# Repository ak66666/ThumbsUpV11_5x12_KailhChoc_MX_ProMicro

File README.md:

# ThumbsUp! v11 5x12 Keyboard for Kailh Choc and MX-compatible switches dirven by ProMicro and pin-compatibles

Multilevel 58 Key Ergonomic Contoured Mechanical Keyboard.

A variant of v5 and v8 for this specific combination of switches, plus with extra pins for MCU to make ProGlide Cirque touchpad work in ZMK.
Added slots on the PCBs to cut off the top row and outer columns, to turn the board into a 4x12 or 5x10 or 4x10, moved the tracks out of the way for those cuts.

The board uses Kailh Choc and MX-compatible switches with hot-swap sockets.

ProMicro or pin-compatible MCUs are supported, including Raspberry RP2040, nice!nano v2 and clones.

Supports Proglide Cirque touchpad (up to 40mm diameter).

Can be made wireless with nice!nano v2 (or a clone) and a battery, [ZMK firmware.](https://github.com/ak66666/zmk-config/tree/master)

# Photos

See more pictures in Photos folder. 

# Firmware
Default firmware is here:

Note this board uses the firmware from v5 - it got the very same wiring.

# Here you can buy it

# More info

Usage instructions and miscellaneous info:

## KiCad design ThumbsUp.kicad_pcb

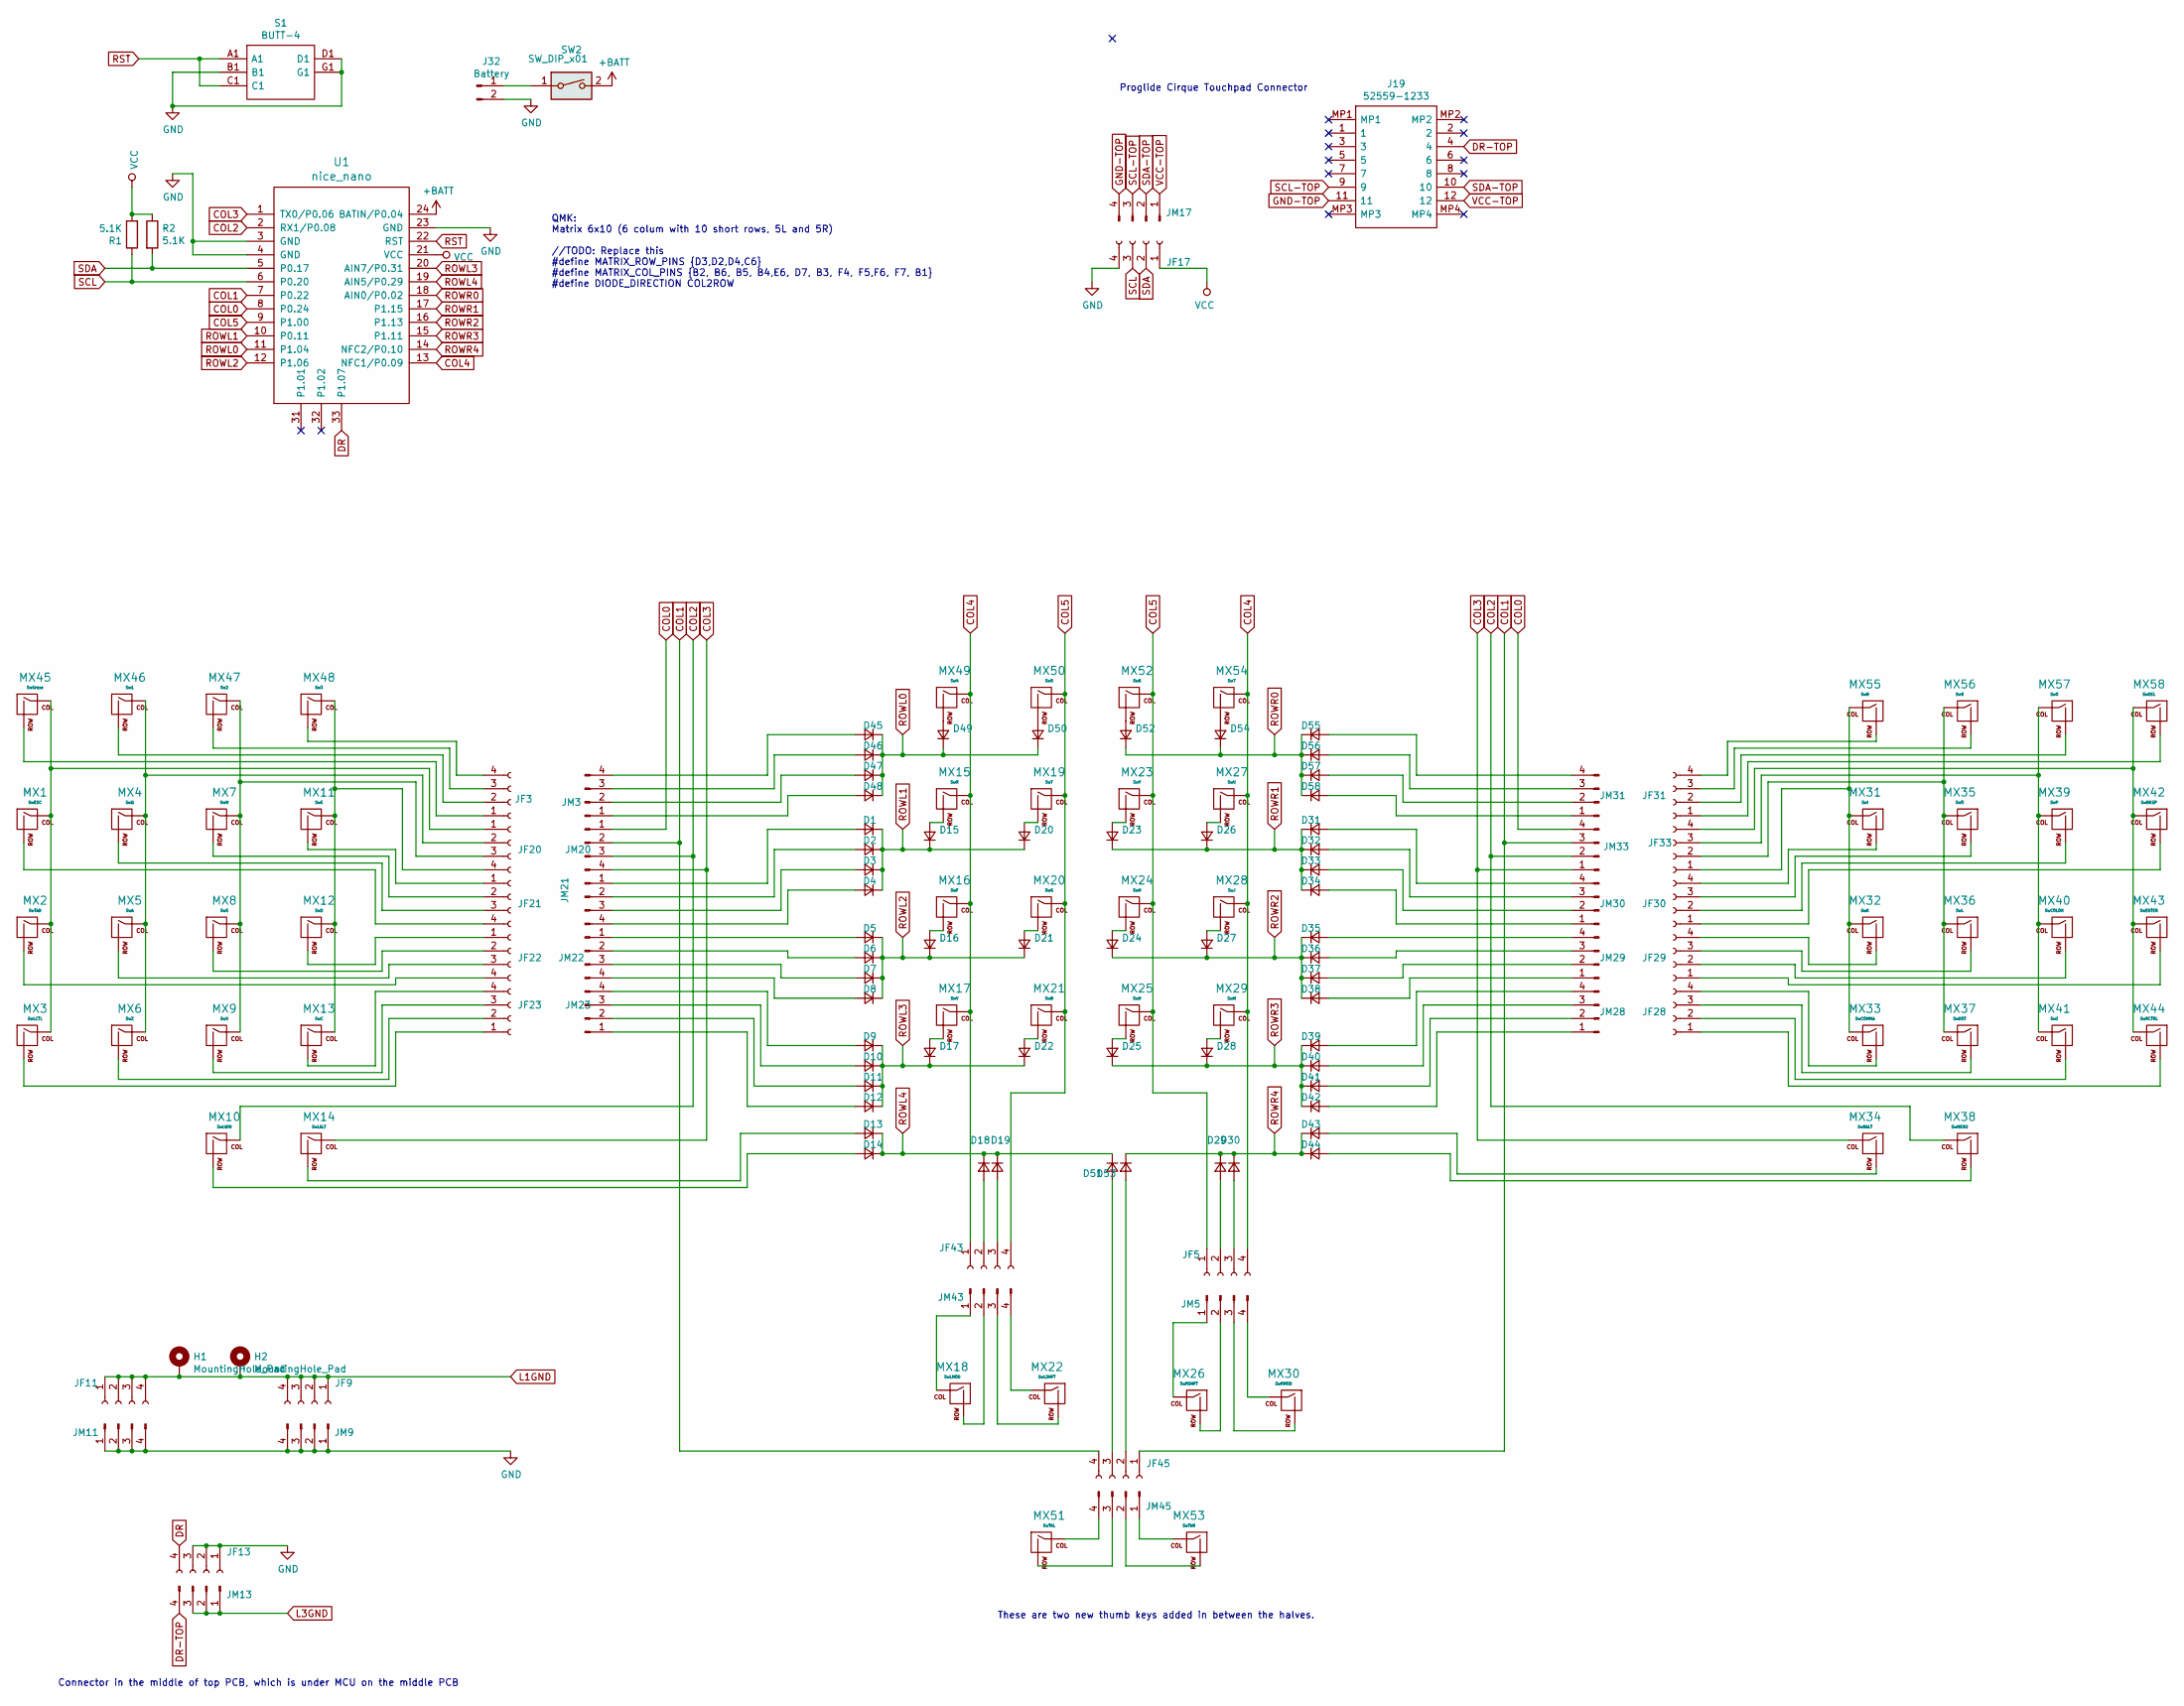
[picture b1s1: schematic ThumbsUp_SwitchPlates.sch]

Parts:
D1, D2, D3, D4, D5, D6, D7, D8, D9, D10, D11, D12, D13, D14, D15, D16, D17, D18, D19, D20, D21, D22, D23, D24, D25, D26, D27, D28, D29, D30, D31, D32, D33, D34, D35, D36, D37, D38, D39, D40, D41, D42, D43, D44, D45, D46, D47, D48, D49, D50, D51, D52, D53, D54, D55, D56, D57, D58: D_Small; D_SOD-523
H1: MountingHole_Pad; MountingHole_6mm_Pad_Via
H2: MountingHole_Pad; MountingHole_8.4mm_M8_Pad_Via
J19: 52559-1233; 525591233; Mouser Part Number 538-52559-1233
J32: Battery; PinHeader_1x02_P2.54mm_Vertical
JF3, JF5, JF20, JF21, JF22, JF23, JF28, JF29, JF30, JF31, JF33, JF43, JF45: Conn_01x04_Female; PinSocket_1x04_P2.54mm_Vertical
JF9, JF11, JF13, JF17: Raiser_Female; PinSocket_1x04_P2.54mm_Vertical
JM3, JM20, JM21, JM22, JM23, JM28, JM29, JM30, JM31, JM33, JM43, JM45: Conn_01x04_Male; PinHeader_1x04_P2.54mm_Vertical
JM5: Male; PinHeader_1x04_P2.54mm_Vertical
JM9, JM11, JM13, JM17: Raiser_Male; PinHeader_1x04_P2.54mm_Vertical
MX1: SwESC; PG1350_MX_sockets
MX2: SwTAB; PG1350_MX_sockets
MX3: SwLCTL; PG1350_MX_sockets
MX4: SwQ; PG1350_MX_sockets
MX5: SwA; PG1350_MX_sockets
MX6: SwZ; PG1350_MX_sockets
MX7: SwW; PG1350_MX_sockets
MX8: SwS; PG1350_MX_sockets
MX9: SwX; PG1350_MX_sockets
MX10: SwLWIN; PG1350_MX_sockets
MX11: SwE; PG1350_MX_sockets
MX12: SwD; PG1350_MX_sockets
MX13: SwC; PG1350_MX_sockets
MX14: SwLALT; PG1350_MX_sockets
MX15: SwR; PG1350_MX_sockets
MX16: SwF; PG1350_MX_sockets
MX17: SwV; PG1350_MX_sockets
MX18: SwLMOD; PG1350_MX_sockets
MX19: SwT; PG1350_MX_sockets
MX20: SwG; PG1350_MX_sockets
MX21: SwB; PG1350_MX_sockets
MX22: SwLSHFT; PG1350_MX_sockets
MX23: SwY; PG1350_MX_sockets
MX24: SwH; PG1350_MX_sockets
MX25: SwN; PG1350_MX_sockets
MX26: SwRSHFT; PG1350_MX_sockets
MX27: SwU; PG1350_MX_sockets
MX28: SwJ; PG1350_MX_sockets
MX29: SwM; PG1350_MX_sockets
MX30: SwRMOD; PG1350_MX_sockets
MX31: SwI; PG1350_MX_sockets
MX32: SwK; PG1350_MX_sockets
MX33: SwCOMMA; PG1350_MX_sockets
MX34: SwRALT; PG1350_MX_sockets
MX35: SwO; PG1350_MX_sockets
MX36: SwL; PG1350_MX_sockets
MX37: SwDOT; PG1350_MX_sockets
MX38: SwMENU; PG1350_MX_sockets
MX39: SwP; PG1350_MX_sockets
MX40: SwCOLON; PG1350_MX_sockets
MX41: Sw?; PG1350_MX_sockets
MX42: SwBKSP; PG1350_MX_sockets
MX43: SwENTER; PG1350_MX_sockets
MX44: SwRCTRL; PG1350_MX_sockets
MX45: SwGrave; PG1350_MX_sockets
MX46: Sw1; PG1350_MX_sockets
MX47: Sw2; PG1350_MX_sockets
MX48: Sw3; PG1350_MX_sockets
MX49: Sw4; PG1350_MX_sockets
MX50: Sw5; PG1350_MX_sockets
MX51: SwThL; PG1350_MX_sockets
MX52: Sw6; PG1350_MX_sockets
MX53: SwThR; PG1350_MX_sockets
MX54: Sw7; PG1350_MX_sockets
MX55: Sw8; PG1350_MX_sockets
MX56: Sw9; PG1350_MX_sockets
MX57: Sw0; PG1350_MX_sockets
MX58: SwDEL; PG1350_MX_sockets
R1, R2: 5.1K; R_0805_2012Metric
S1: BUTT-4; BUTT4; Manufacturer_Part_Number BUTT-4; Mouser Part Number 992-BUTT-4
SW2: SW_DIP_x01; 18252321
U1: nice_nano

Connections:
+BATT: SW2.2, U1.24 (BATIN/P0.04)
COL0: JM20.1, JM33.4, U1.8 (P0.24)
COL1: JF45.1, JF45.4, JM20.2, JM33.3, U1.7 (P0.22)
COL2: JM20.3, JM33.2, MX10.1 (COL), MX38.1 (COL), U1.2 (RX1/P0.08)
COL3: JM20.4, JM33.1, MX14.1 (COL), MX34.1 (COL), U1.1 (TX0/P0.06)
COL4: JF5.4, JF43.1, MX15.1 (COL), MX16.1 (COL), MX17.1 (COL), MX27.1 (COL), MX28.1 (COL), MX29.1 (COL), MX49.1 (COL), MX54.1 (COL), U1.13 (NFC1/P0.09)
COL5: JF5.1, JF43.4, MX19.1 (COL), MX20.1 (COL), MX21.1 (COL), MX23.1 (COL), MX24.1 (COL), MX25.1 (COL), MX50.1 (COL), MX52.1 (COL), U1.9 (P1.00)
DR: JF13.4, U1.33 (P1.07)
DR-TOP: J19.4, JM13.4
GND: J32.2, JF13.1, JF13.2, JF13.3, JF17.4, JM9.1, JM9.2, JM9.3, JM9.4, JM11.1, JM11.2, JM11.3, JM11.4, S1.B1, S1.D1, S1.G1, U1.3 (GND), U1.4 (GND), U1.23 (GND)
GND-TOP: J19.11, JM17.4
L1GND: H1.1, H2.1, JF9.1, JF9.2, JF9.3, JF9.4, JF11.1, JF11.2, JF11.3, JF11.4
L3GND: JM13.1, JM13.2, JM13.3
unnamed: D1.2 (A), JM21.1
unnamed: D2.2 (A), JM21.2
unnamed: D3.2 (A), JM21.3
unnamed: D4.2 (A), JM21.4
unnamed: D5.2 (A), JM22.1
unnamed: D6.2 (A), JM22.2
unnamed: D7.2 (A), JM22.3
unnamed: D8.2 (A), JM22.4
unnamed: D9.2 (A), JM23.4
unnamed: D10.2 (A), JM23.3
unnamed: D11.2 (A), JM23.2
unnamed: D12.2 (A), JM23.1
unnamed: D13.2 (A), MX14.2 (ROW)
unnamed: D14.2 (A), MX10.2 (ROW)
unnamed: D15.2 (A), MX15.2 (ROW)
unnamed: D16.2 (A), MX16.2 (ROW)
unnamed: D17.2 (A), MX17.2 (ROW)
unnamed: D18.2 (A), JF43.2
unnamed: D19.2 (A), JF43.3
unnamed: D20.2 (A), MX19.2 (ROW)
unnamed: D21.2 (A), MX20.2 (ROW)
unnamed: D22.2 (A), MX21.2 (ROW)
unnamed: D23.2 (A), MX23.2 (ROW)
unnamed: D24.2 (A), MX24.2 (ROW)
unnamed: D25.2 (A), MX25.2 (ROW)
unnamed: D26.2 (A), MX27.2 (ROW)
unnamed: D27.2 (A), MX28.2 (ROW)
unnamed: D28.2 (A), MX29.2 (ROW)
unnamed: D29.2 (A), JF5.2
unnamed: D30.2 (A), JF5.3
unnamed: D31.2 (A), JM30.4
unnamed: D32.2 (A), JM30.3
unnamed: D33.2 (A), JM30.2
unnamed: D34.2 (A), JM30.1
unnamed: D35.2 (A), JM29.4
unnamed: D36.2 (A), JM29.3
unnamed: D37.2 (A), JM29.2
unnamed: D38.2 (A), JM29.1
unnamed: D39.2 (A), JM28.4
unnamed: D40.2 (A), JM28.3
unnamed: D41.2 (A), JM28.2
unnamed: D42.2 (A), JM28.1
unnamed: D43.2 (A), MX34.2 (ROW)
unnamed: D44.2 (A), MX38.2 (ROW)
unnamed: D45.2 (A), JM3.4
unnamed: D46.2 (A), JM3.3
unnamed: D47.2 (A), JM3.2
unnamed: D48.2 (A), JM3.1
unnamed: D49.2 (A), MX49.2 (ROW)
unnamed: D50.2 (A), MX50.2 (ROW)
unnamed: D51.2 (A), JF45.3
unnamed: D52.2 (A), MX52.2 (ROW)
unnamed: D53.2 (A), JF45.2
unnamed: D54.2 (A), MX54.2 (ROW)
unnamed: D55.2 (A), JM31.4
unnamed: D56.2 (A), JM31.3
unnamed: D57.2 (A), JM31.2
unnamed: D58.2 (A), JM31.1
unnamed: J32.1, SW2.1
unnamed: JF3.1, MX45.2 (ROW)
unnamed: JF3.2, MX46.2 (ROW)
unnamed: JF3.3, MX47.2 (ROW)
unnamed: JF3.4, MX48.2 (ROW)
unnamed: JF20.1, MX1.1 (COL), MX2.1 (COL), MX3.1 (COL), MX45.1 (COL)
unnamed: JF20.2, MX4.1 (COL), MX5.1 (COL), MX6.1 (COL), MX46.1 (COL)
unnamed: JF20.3, MX7.1 (COL), MX8.1 (COL), MX9.1 (COL), MX47.1 (COL)
unnamed: JF20.4, MX11.1 (COL), MX12.1 (COL), MX13.1 (COL), MX48.1 (COL)
unnamed: JF21.1, MX11.2 (ROW)
unnamed: JF21.2, MX7.2 (ROW)
unnamed: JF21.3, MX4.2 (ROW)
unnamed: JF21.4, MX1.2 (ROW)
unnamed: JF22.1, MX12.2 (ROW)
unnamed: JF22.2, MX8.2 (ROW)
unnamed: JF22.3, MX5.2 (ROW)
unnamed: JF22.4, MX2.2 (ROW)
unnamed: JF23.1, MX3.2 (ROW)
unnamed: JF23.2, MX6.2 (ROW)
unnamed: JF23.3, MX9.2 (ROW)
unnamed: JF23.4, MX13.2 (ROW)
unnamed: JF28.1, MX44.2 (ROW)
unnamed: JF28.2, MX41.2 (ROW)
unnamed: JF28.3, MX37.2 (ROW)
unnamed: JF28.4, MX33.2 (ROW)
unnamed: JF29.1, MX43.2 (ROW)
unnamed: JF29.2, MX40.2 (ROW)
unnamed: JF29.3, MX36.2 (ROW)
unnamed: JF29.4, MX32.2 (ROW)
unnamed: JF30.1, MX42.2 (ROW)
unnamed: JF30.2, MX39.2 (ROW)
unnamed: JF30.3, MX35.2 (ROW)
unnamed: JF30.4, MX31.2 (ROW)
unnamed: JF31.1, MX58.2 (ROW)
unnamed: JF31.2, MX57.2 (ROW)
unnamed: JF31.3, MX56.2 (ROW)
unnamed: JF31.4, MX55.2 (ROW)
unnamed: JF33.1, MX31.1 (COL), MX32.1 (COL), MX33.1 (COL), MX55.1 (COL)
unnamed: JF33.2, MX35.1 (COL), MX36.1 (COL), MX37.1 (COL), MX56.1 (COL)
unnamed: JF33.3, MX39.1 (COL), MX40.1 (COL), MX41.1 (COL), MX57.1 (COL)
unnamed: JF33.4, MX42.1 (COL), MX43.1 (COL), MX44.1 (COL), MX58.1 (COL)
unnamed: JM5.1, MX26.1 (COL)
unnamed: JM5.2, MX26.2 (ROW)
unnamed: JM5.3, MX30.2 (ROW)
unnamed: JM5.4, MX30.1 (COL)
unnamed: JM43.1, MX18.1 (COL)
unnamed: JM43.2, MX18.2 (ROW)
unnamed: JM43.3, MX22.2 (ROW)
unnamed: JM43.4, MX22.1 (COL)
unnamed: JM45.1, MX53.1 (COL)
unnamed: JM45.2, MX53.2 (ROW)
unnamed: JM45.3, MX51.2 (ROW)
unnamed: JM45.4, MX51.1 (COL)
ROWL0: D45.1 (K), D46.1 (K), D47.1 (K), D48.1 (K), D49.1 (K), D50.1 (K), U1.11 (P1.04)
ROWL1: D1.1 (K), D2.1 (K), D3.1 (K), D4.1 (K), D15.1 (K), D20.1 (K), U1.10 (P0.11)
ROWL2: D5.1 (K), D6.1 (K), D7.1 (K), D8.1 (K), D16.1 (K), D21.1 (K), U1.12 (P1.06)
ROWL3: D9.1 (K), D10.1 (K), D11.1 (K), D12.1 (K), D17.1 (K), D22.1 (K), U1.20 (AIN7/P0.31)
ROWL4: D13.1 (K), D14.1 (K), D18.1 (K), D19.1 (K), D51.1 (K), U1.19 (AIN5/P0.29)
ROWR0: D52.1 (K), D54.1 (K), D55.1 (K), D56.1 (K), D57.1 (K), D58.1 (K), U1.18 (AIN0/P0.02)
ROWR1: D23.1 (K), D26.1 (K), D31.1 (K), D32.1 (K), D33.1 (K), D34.1 (K), U1.17 (P1.15)
ROWR2: D24.1 (K), D27.1 (K), D35.1 (K), D36.1 (K), D37.1 (K), D38.1 (K), U1.16 (P1.13)
ROWR3: D25.1 (K), D28.1 (K), D39.1 (K), D40.1 (K), D41.1 (K), D42.1 (K), U1.15 (P1.11)
ROWR4: D29.1 (K), D30.1 (K), D43.1 (K), D44.1 (K), D53.1 (K), U1.14 (NFC2/P0.10)
RST: S1.A1, S1.C1, U1.22 (RST)
SCL: JF17.3, R1.1, U1.6 (P0.20)
SCL-TOP: J19.9, JM17.3
SDA: JF17.2, R2.2, U1.5 (P0.17)
SDA-TOP: J19.10, JM17.2
VCC: JF17.1, R1.2, R2.1, U1.21 (VCC)
VCC-TOP: J19.12, JM17.1

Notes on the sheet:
QMK: Matrix 6x10 (6 colum with 10 short rows, 5L and 5R) //TODO: Replace this #define MATRIX_ROW_PINS {D3,D2,D4,C6} #define MATRIX_COL_PINS {B2, B6, B5, B4,E6, D7, B3, F4, F5,F6, F7, B1} #define DIODE_DIRECTION COL2ROW
Proglide Cirque Touchpad Connector
These are two new thumb keys added in between the halves.
Connector in the middle of top PCB, which is under MCU on the middle PCB

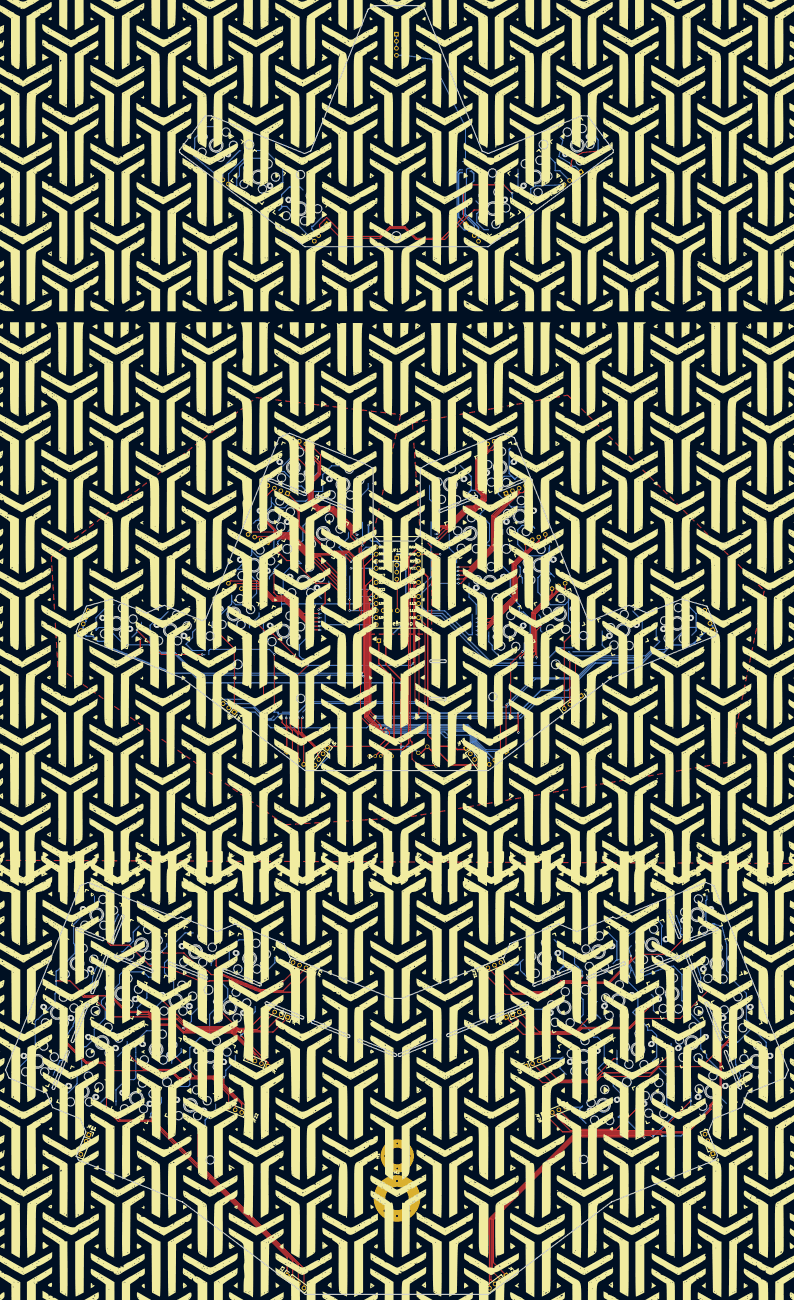
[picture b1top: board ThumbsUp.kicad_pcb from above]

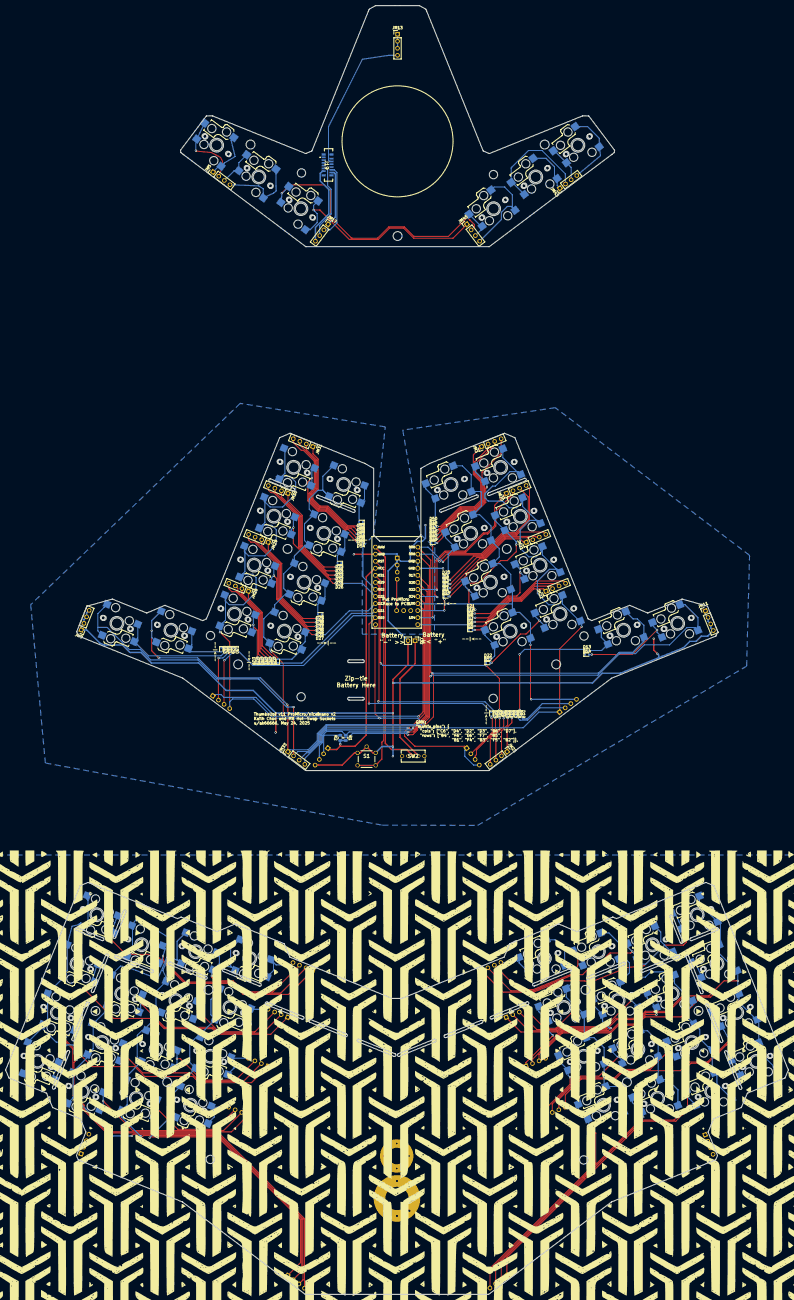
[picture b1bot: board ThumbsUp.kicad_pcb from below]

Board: 2 copper layers, 282.0 x 464.4 mm, 159 parts (81 on the bottom side), 141 nets.

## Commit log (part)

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2025-05-24 Cloned v8 into v11, no changes to the design yet.
2025-05-24 Updated the schematics, replaced the switches with MX/Kailh Choc combo
2025-05-25 Replaced the diodes to the tiny D523 ones, started the tracks.
2025-05-26 Laid out the middle PCB.
2025-05-26 Added connector holes for the switch panels.
2025-05-26 Laid out the top PCB.
2025-05-27 Laid out the bottom PCB.
2025-05-27 Added a project for the switch plates.
2025-05-27 Added silkscreens.
2025-05-28 Added solder mask areas to trim the silkscreen outside of the pcb.
2025-05-28 Added solder mask areas to trim the silkscreen outside of the pcb - for L2.
2025-05-28 Generated Gerbers for all three switch plates which were accepted by JLCPCB without extra 'large size' charges.
2025-05-28 Added the diode direction wherever it was missed.
2025-05-28 Corrected two switch support plates as per JLCPCB'S FEEDBACK..
2025-06-06 Added photos of v11 in different stages of readiness.
2025-06-07 Added photos references into readme.
2026-05-29 v11: Added STEP file for the bottom board outline
